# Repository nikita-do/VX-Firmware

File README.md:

# VitalX Firmware

This repository contains the firmware for the pain detection device based on ECG, PPG and EDA/GSR signals. The implementation focuses on reading these from hardware, batching them in memory, packaging, and sending them to a remote broker for analysis and visualization.

### 1. Sensor acquisition

The firmware reads two categories of signals:

- GSR and ECG through the ESP32 ADC inputs
- IR and red PPG values through the ADPD144 sensor

The code uses:

- ADC calibration for reliable analog-to-digital conversion
- oneshot ADC configuration for low-overhead sampling
- FreeRTOS timers to trigger sensor reads at a fixed rate

Current runtime configuration:

- Sampling rate: 512 Hz
- Batch size: 512 samples
- Payload encoding: CBOR

### 2. Real-time buffering

The firmware uses circular buffers to handle continuous sampling without blocking or dropping data. Each signal stream has its own buffer:

- GSR buffer
- ECG buffer
- IR buffer
- Red buffer

The sensor task writes samples continuously, and the publish task reads out a full batch later for encoding and publishing.

### 3. MQTT communication

The device communicates with a secure MQTT broker using the ESP-IDF MQTT client. The implementation is built around asynchronous event handling, the firmware reacts to connection events, subscriptions, received commands, and errors without blocking the main data path.

The firmware publishes:

- device online status
- firmware version
- sampling metadata
- RSSI information
- CBOR-encoded sensor batches

It also subscribes to command topics to support remote control:

- start data publishing
- stop data publishing
- restart/reset the device

The topic design is intentionally device-scoped, so each ESP32 instance keeps its own data stream and command channels. The device topics are highlighted below.

### 4. Wi-Fi provisioning and connectivity

The device includes Wi-Fi provisioning support using the ESP-IDF provisioning framework. The firmware can be configured at runtime instead of hardcoding credentials into firmware.

The implementation includes:

- SoftAP or BLE provisioning flow
- QR-provisioning support
- NVS-backed credential storage
- reconnect logic after connection loss
- reset/reprovisioning support

### 5. Time synchronization

The firmware synchronizes the local clock using SNTP before producing timestamped sensor packets. This matters because the sensor data is grouped into batches and then published to MQTT. Without a valid time source, the downstream analytics side has no reliable chronology for the readings.

### 6. Device health and operational status

The firmware also includes a few common reliability features:

- LED status indication for connection state
- last-will MQTT messages for offline detection
- restart after repeated disconnects
- optional heap monitoring for debugging memory issues

## Firmware structure

```text
firmware/
└── esp32-VitalX/
    ├── CMakeLists.txt
    ├── sdkconfig
    ├── components/
    │   └── adpd144/
    ├── main/
    │   ├── app_main.c
    │   ├── app_main.h
    │   ├── app_adc.c
    │   ├── app_mqtt.c
    │   ├── app_time.c
    │   ├── circular_buffer.c
    │   ├── wifi_prov.c
    │   ├── Kconfig.projbuild
    │   └── idf_component.yml
    └── managed_components/
```

Key firmware files:

- app_main.c: main application loop, sensor batching, MQTT control, task scheduling
- app_adc.c: ADC calibration and reading logic
- app_mqtt.c: MQTT client configuration and event handling
- app_time.c: SNTP and timestamp handling
- wifi_prov.c: Wi-Fi provisioning and connection flow
- circular_buffer.c: ring-buffer implementation for the sensor streams
- Kconfig.projbuild: custom project configuration for MQTT and Wi-Fi settings

## Build notes

This project uses the ESP-IDF framework and is configured as an ESP32-S2 firmware target.

## References

- ESP-IDF: https://docs.espressif.com/projects/esp-idf/en/latest/esp32/index.html
- ESP SoftAP Provisioning:
https://play.google.com/store/apps/details?id=com.espressif.provsoftap&pcampaignid=web_s
hare
- FreeRTOS: https://www.freertos.org/media/2018/FreeRTOS_Reference_Manual_V10.0.0.pdf
- CBOR Encoding: https://cborbook.com/part_1/practical_introduction_to_cbor.html

---

This README summarizes the implementation that was completed in the current firmware codebase.

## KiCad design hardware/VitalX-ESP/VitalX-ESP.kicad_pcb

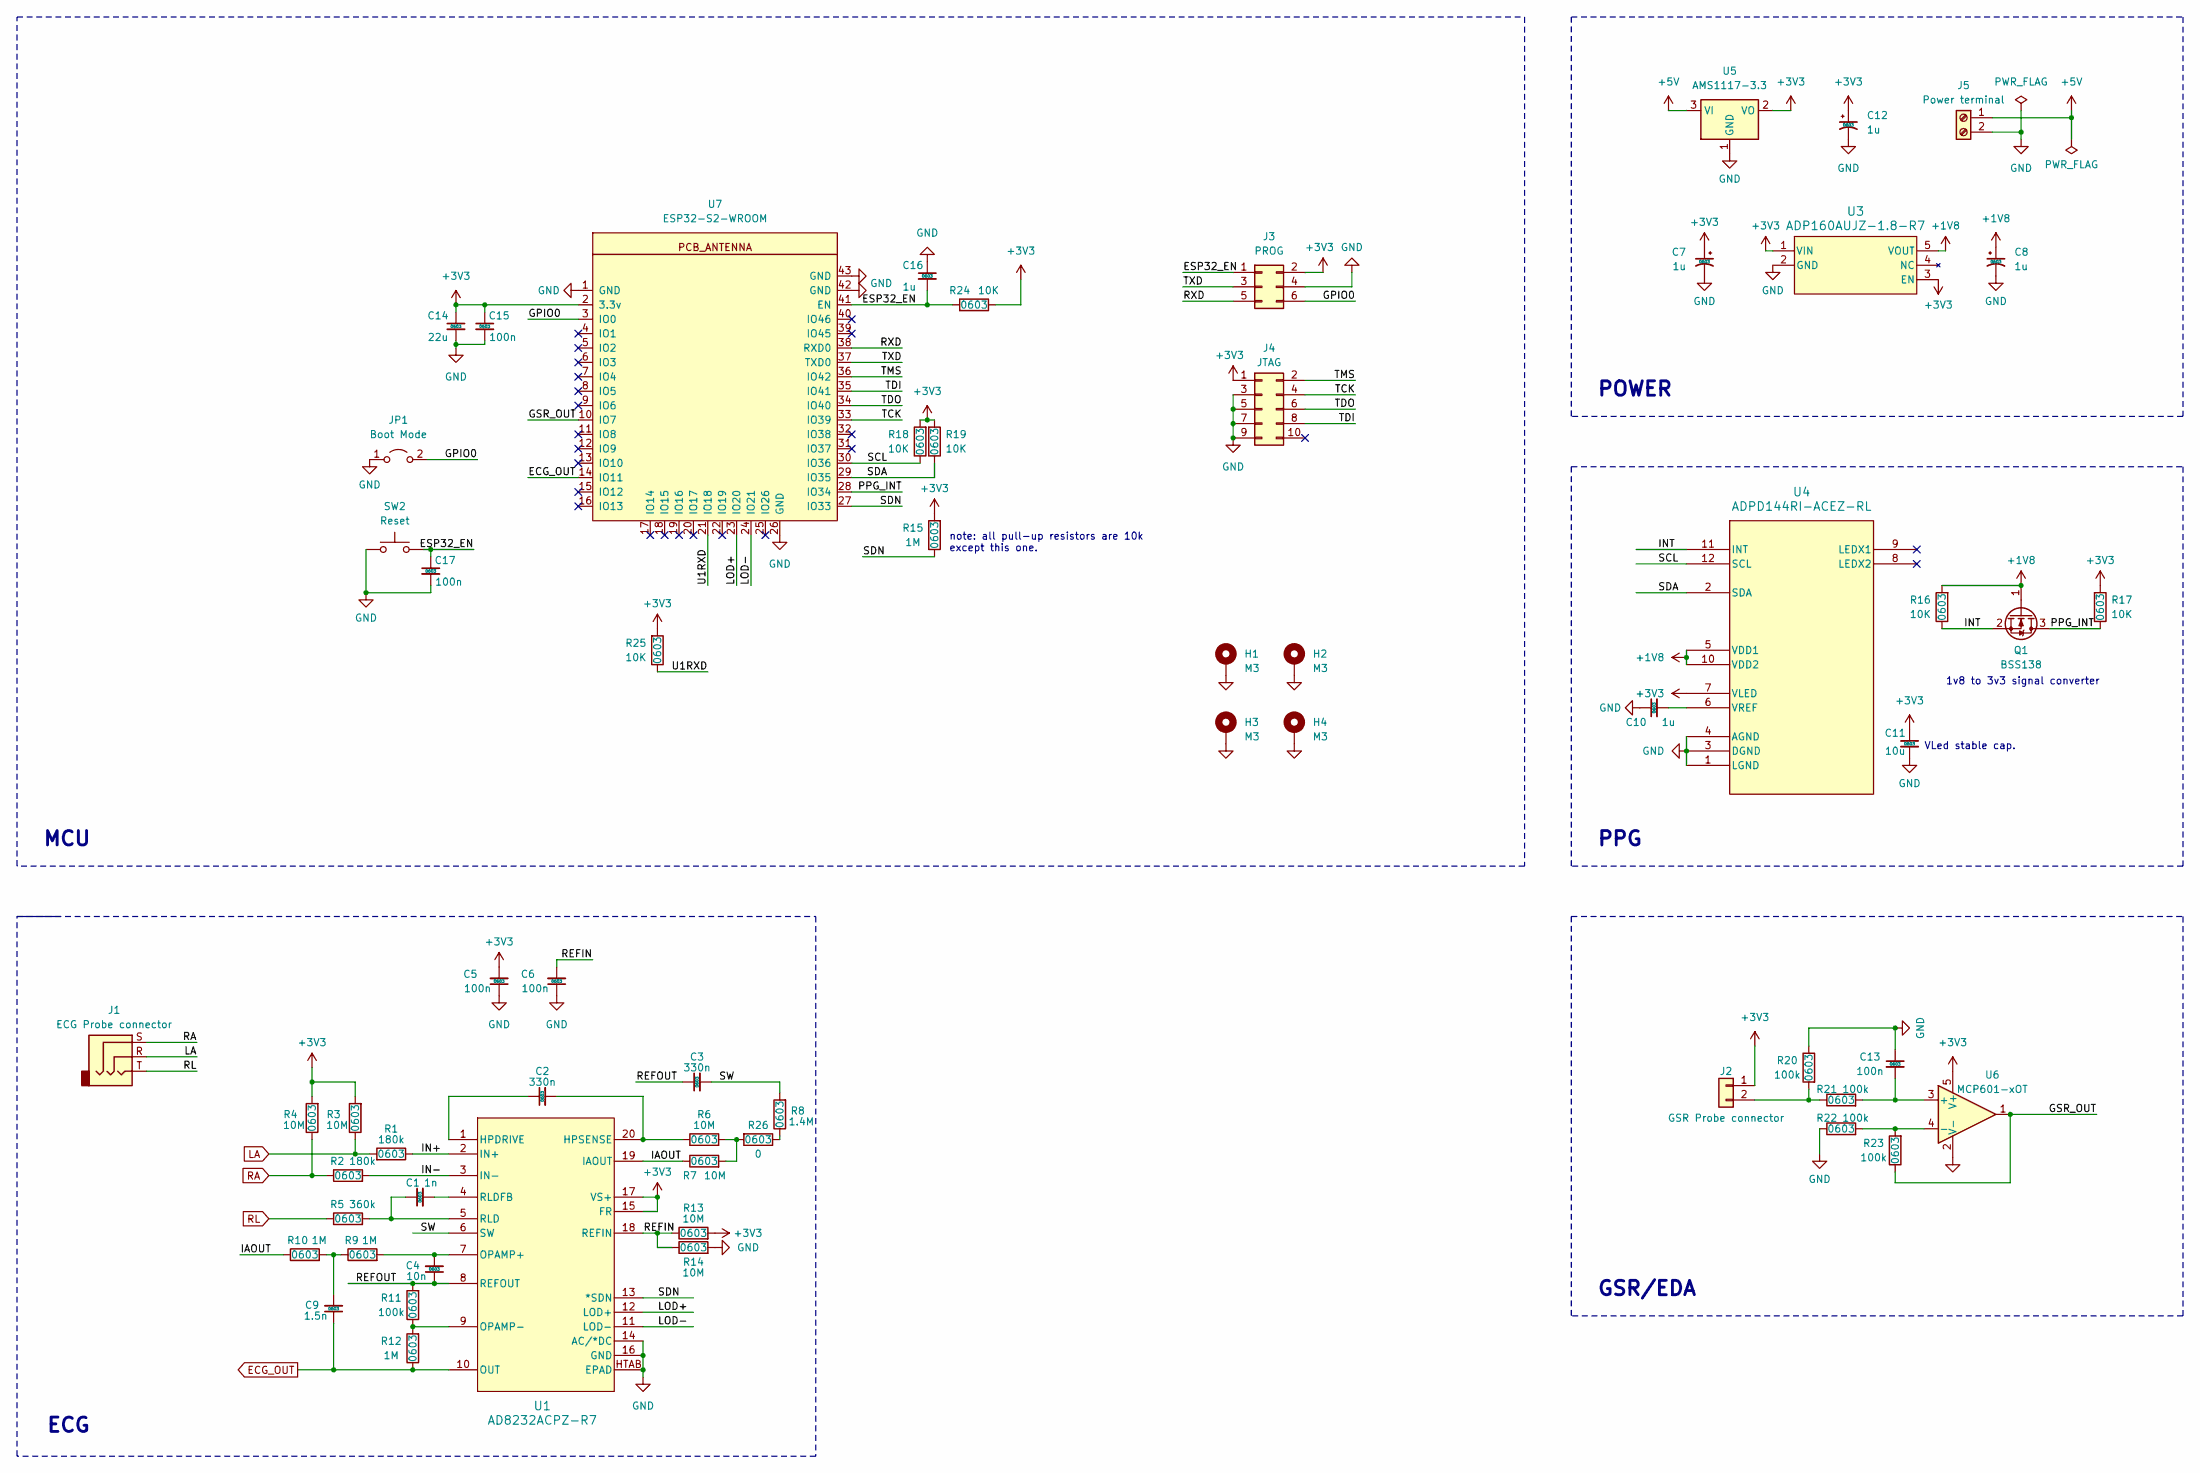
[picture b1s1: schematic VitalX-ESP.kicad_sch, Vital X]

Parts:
C1: 1n; C_0603_1608Metric
C2, C3: 330n; C_0603_1608Metric
C4: 10n; C_0603_1608Metric
C5, C6, C13, C15, C17: 100n; C_0603_1608Metric
C7, C8, C10, C12, C16: 1u; C_0603_1608Metric
C9: 1.5n; C_0603_1608Metric
C11: 10u; C_0603_1608Metric
C14: 22u; C_0603_1608Metric
H1, H2, H3, H4: M3; MountingHole_3.2mm_M3_Pad_Via
J1: ECG Probe connector; SJ2-3593D-SMT-TR
J2: GSR Probe connector; PinHeader_1x02_P2.54mm_Vertical
J3: PROG; PinHeader_2x03_P2.54mm_Vertical
J4: JTAG; PinHeader_2x05_P2.54mm_Vertical
J5: Power terminal; TerminalBlock_bornier-2_P5.08mm
JP1: Boot Mode; PinHeader_1x02_P2.54mm_Vertical
Q1: BSS138; SOT-23; mouser mnf num 512-BSS138
R1, R2: 180k; R_0603_1608Metric
R3, R4, R6, R7, R13, R14: 10M; R_0603_1608Metric
R5: 360k; R_0603_1608Metric
R8: 1.4M; R_0603_1608Metric
R9, R10, R12, R15: 1M; R_0603_1608Metric
R11, R20, R21, R22, R23: 100k; R_0603_1608Metric
R16, R17, R18, R19, R24, R25: 10K; R_0603_1608Metric
R26: 0; R_0603_1608Metric
SW2: Reset; SW_Tactile_SPST_NO_Straight_CK_PTS636Sx25SMTRLFS
U1: AD8232ACPZ-R7; AD8232ACPZ; mouser mnf num 584-AD8232ACPZ-R7
U3: ADP160AUJZ-1.8-R7; ADP160AUJZ-1-8-R7; mouser mnf num 584-ADP160AUJZ-1.8R7
U4: ADPD144RI-ACEZ-RL; CE-12-2_ADI; mouser mnf num 584-ADPD144RI-ACEZRL
U5: AMS1117-3.3; SOT-223-3_TabPin2; mouser mnf num 926-LM1117MPX3.3NOPB
U6: MCP601-xOT; SOT-23-5; mouser mnf num 579-MCP601RT-E/OT
U7: ESP32-S2-WROOM; esp32-s2-wrooom; mouser mnf num 356-ESP32S2WRMI320US

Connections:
+1V8: C8.1, Q1.1 (G), R16.2, U3.5 (VOUT), U4.5 (VDD1), U4.10 (VDD2)
+3V3: C5.2, C7.1, C11.1, C12.1, C14.1, C15.1, J2.1, J3.2, J4.1, R3.2, R4.2, R13.2, R15.2, R17.2, R18.2, R19.2, R24.1, R25.2, U1.15 (FR), U1.17 (VS+), U3.1 (VIN), U3.3 (EN), U4.7 (VLED), U5.2 (VO), U6.5 (V+), U7.2 (3.3v)
+5V: J5.1, U5.3 (VI)
/ESP32_EN: C16.2, C17.1, J3.1, R24.2, SW2.2, U7.41 (EN)
/GPIO0: J3.6, JP1.2 (B), U7.3 (IO0)
/GSR_OUT: R23.1, U6.1, U7.10 (IO7)
/IAOUT: R7.1, R10.1, U1.19 (IAOUT)
/IN+: R1.1, U1.2 (IN+)
/IN-: R2.2, U1.3 (IN-)
/INT: Q1.2 (S), R16.1, U4.11 (INT)
/LOD+: U1.12 (LOD+), U7.23 (IO20)
/LOD-: U1.11 (LOD-), U7.24 (IO21)
/PPG_INT: Q1.3 (D), R17.1, U7.28 (IO34)
/REFIN: C6.2, R13.1, R14.1, U1.18 (REFIN)
/REFOUT: C3.1, C4.1, R11.2, U1.8 (REFOUT)
/RXD: J3.5, U7.38 (RXD0)
/SCL: R18.1, U4.12 (SCL), U7.30 (IO36)
/SDA: R19.1, U4.2 (SDA), U7.29 (IO35)
/SDN: R15.1, U1.13 (*SDN), U7.27 (IO33)
/SW: C3.2, R8.2, U1.6 (SW)
/TCK: J4.4, U7.33 (IO39)
/TDI: J4.8, U7.35 (IO41)
/TDO: J4.6, U7.34 (IO40)
/TMS: J4.2, U7.36 (IO42)
/TXD: J3.3, U7.37 (TXD0)
/U1RXD: R25.1, U7.21 (IO18)
ECG_OUT: C9.1, R12.1, U1.10 (OUT), U7.14 (IO11)
GND: C5.1, C6.1, C7.2, C8.2, C10.1, C11.2, C12.2, C13.1, C14.2, C15.2, C16.1, C17.2, H1.1, H2.1, H3.1, H4.1, J3.4, J4.3, J4.5, J4.7, J4.9, J5.2, JP1.1 (A), R14.2, R20.1, R22.1, SW2.1, U1.14 (AC/*DC), U1.16 (GND), U1.HTAB (EPAD), U3.2 (GND), U4.1 (LGND), U4.3 (DGND), U4.4 (AGND), U5.1 (GND), U6.2 (V-), U7.1 (GND), U7.26 (GND), U7.42 (GND), U7.43 (GND)
LA: J1.R, R1.2, R3.1
unnamed: C9.2, R9.1, R10.2
unnamed: J2.2, R20.2, R21.1
unnamed: R8.1, R26.1
unnamed: R6.2, R7.2, R26.2
unnamed: C2.1, U1.1 (HPDRIVE)
unnamed: C2.2, R6.1, U1.20 (HPSENSE)
unnamed: C4.2, R9.2, U1.7 (OPAMP+)
unnamed: R11.1, R12.2, U1.9 (OPAMP-)
unnamed: C1.1, R5.2, U1.5 (RLD)
unnamed: C1.2, U1.4 (RLDFB)
unnamed: C10.2, U4.6 (VREF)
unnamed: C13.2, R21.2, U6.3 (+)
unnamed: R22.2, R23.2, U6.4 (-)
RA: J1.S, R2.1, R4.1
RL: J1.T, R5.1

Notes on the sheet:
MCU
PPG
1v8 to 3v3 signal converter
GSR/EDA
ECG
VLed stable cap.
note: all pull-up resistors are 10k except this one.
POWER

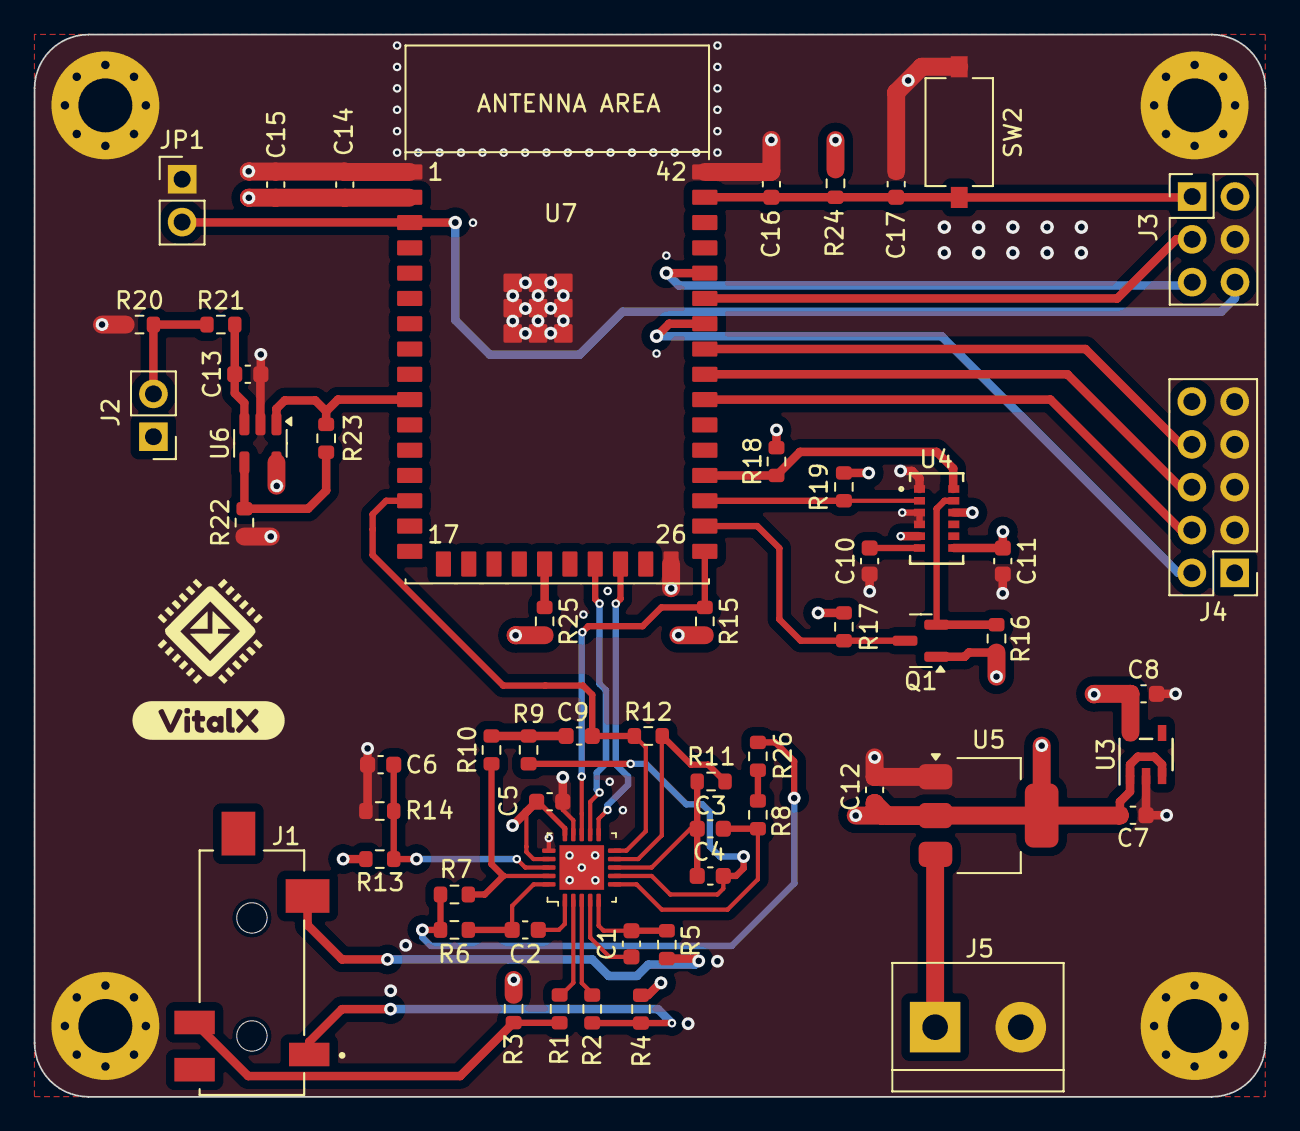
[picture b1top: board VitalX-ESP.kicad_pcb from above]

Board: 4 copper layers, 73.0 x 63.0 mm, 62 parts (0 on the bottom side), 44 nets.

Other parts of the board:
kibuzzard-673C1CE7: G***; kibuzzard-673C1CE7

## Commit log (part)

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2024-01-05 Initialize project
2024-07-22 Init hardware project
2024-07-22 Update Environment path.
2024-07-22 [VTX-5] Update gitignore. Remove *.kicad_prl
2024-07-22 [VTX-5] Update Logo path.
2024-07-25 [VTX-5] Finalize ECG Block. Minor changes: - Remove cache, bak files. - Change AD8232's EPAD electrical type for ERC. - Update footprint path.
2024-07-30 [VTX-6] Minor changes to 3D models path.
2024-08-05 [VTX-6] Add symbol/footprint.
    Added ADPD144RI PPG symbol and footprint.
2024-08-05 [VTX-6] Initialize PPG Block.
    Initial implementation of ADPD144RI.
2024-08-24 [VTX-6] Finalize PPG Block.
    Included AMS1117-3.3V voltage regulator.
    Increased Vled capacitor from 1uF to 10uF.
    Pull up resistor on ADPD144RI I2C line.
2024-08-26 [VTX-7] Initialize GSR Block.
    Initial implementation of GSR/EDA readout circuit.
2024-08-26 [nightly] ESP32-WROOM -> ESP32-S2-WROOM
2024-08-26 [nightly] Initial esp32-s2-wroom configuration.
2024-08-26 [nightly] Update Readme.
2024-08-27 [nightly] Connect peripherals.
2024-08-30 [nightly] Finalize schematic, ERC exclutions.
    Exclude typical power-in power-out ERC errors.
2024-08-30 [nightly] Asign footprint.
2024-08-31 [nightly] Finalize schematic.
    Added power connector.
2024-09-01 [nightly] Solving ERC.
2024-09-01 [nightly] Initial PCB layout.
    4 layer stack up:
    - Signal
    - GND
    - GND
    - Signal
    Currently working on ECG Block.
2024-09-04 [nightly] Change ECG Probe connector.
    Utilized PJ-320D for ECG Probe connector.
2024-09-04 [nightly] Inital signals routing.
    First iteration of signals (only) routing.
2024-09-06 [nightly] Change naming convertion.
    +3.3V -> +3V3.
2024-09-06 [nightly] Finalize board layout.
2024-09-06 [nightly] Change ECG Probe footprint.
    Changes in accordance with reference design.
    - https://www.snapeda.com/parts/SJ2-3593D-SMT-TR/CUI%20Devices/view-part/?ref=mouser
    - https://easyeda.com/editor#project_id=8294b8a1d6874413ae900972098163d6
2024-09-06 [nightly] Resolve DRC.
2024-09-13 [nightly] Switch to through via only.
2024-09-13 [nightly] Adhere to the ECG connector standard.
    Mimic Adafruit ECG probe connector design.
2024-09-15 [nighly] Various PCB update.
    PCB stack-up change: Signal-GND-Power(3.3V)-Signal
    Track width in mil: 10, 15, 20, 42
    Via size in mil(dia/hole): 20/10, 15/30
    Show ECG Probe 3D model
    Obfuscate 1.8V track
2024-09-20 [nightly] Program/Debug interface.
    Implementing proper program connector (2x3) and jtag (2x5)
2024-09-29 [nightly] Various footprint update.
    Change footprints:
    - Reset button
    - GSR conn header
    Minor PCB changes:
    - Increase thermal relief via size
2024-09-30 [nightly] Various footprint update.
    Footprint changes:
    - Boot select SMD -> Through-hole
2024-10-06 [nightly] ESP32-S2-WROOM 3d model
2024-10-06 [nightly] Finallize PCB
    Seperate Antenna ground plane
    Add grounded mounting hole
    Add logo
2024-11-19 Update for fabrication: Add top&bot layer mass, change logo, add GND vias, refine text
2024-11-19 [nightly] Update relative path
2025-03-19 mqtt-ssl over hivemq cloud + Python script to save csv file
2025-04-02 add wifi config mode with given ssid and password
2025-04-03 send data as a batch of sensor readings, Fs = 100Hz
2025-04-06 update software code: plotting with pyqtgraph
2025-04-12 Firmware update: WiFi Provisioning
    - remove wifi_stat with hardcoded credentials
    - restart esp32 and clear nvs when disconnected from AP
    - modify service name with prefix VX_ (VitalX)
2025-04-13 Firmware update: version 0.2.0
    - restructure mqtt topics
    - add led indicator for wifi connectivity
2025-04-16 Firmware: v0.2.1
    - Increased sampling rate to 250 Hz.
    - Encoded data as CBOR before sending to MQTT broker.
    - Improved LED indicator
    - Published sampling rate and number of samples per batch to MQTT
    Update .gitignore
2025-05-04 add circular buffer to store data
2025-05-04 update sampling rate to 512 Hz
2025-05-13 firmware updated: bug fixed (v0.2.2)
    - Fixed bug related to circular buffer
    - Added feature: specific device id for topic name
    firmware v0.2.2
2025-05-18 bug fixed: not publish device ID
2025-05-30 firmware v0.3.0 - 3s/batch, fs = 512 Hz
2025-07-17 add packet_id, epoch timestamp, change led_gpio
2025-07-19 modify topic
2025-07-24 temp_array to store buffer value, 1s/batch
